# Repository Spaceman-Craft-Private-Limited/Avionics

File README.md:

Here the explanation of the uploaded .ino files content.
1. 80kv_BLDC.ino - In this file the code is written for a 80kv BLDC motor controlled by a 7Semi BLDC Motor Driver using ESP32 Dev kit.
The GPIO pin connections from 7semi BLDC driver to ESP32 are mentioned in the Code itself as Commented line.
2. all_in_one-damper_repulsion.ino - In this file the code is written for whole the prototype circuit, and in this file two types of code were written.
The first type is written that the stepper motor is controlled by the TB6600 motor driver and the whole code is commented.
The Second type is the code that the stepper motor is controlled by A4988 stepper motor driver and the whole code uncommented.
All the circuit connection is mentioned in the code itself and the Microcontroller used for this whole system is ESP32 Dev kit.
3. small_prototype_system_code_70rpm_noattraction.ino -  In this file the code is written to control the stepper motor by A4988 motor driver using Arduino uno microcontroller.
The term noattraction means the relay is always on, So the electromagnet connected in relay is always energized.
All the pins configurations are mentioned in the code itself.
4. small_prototype_system_code_70rpm_withattraction.ino - In this file the code is written to control the stepper motor by A4988 motor driver using Arduino uno microcontroller.
The term withattraction means the relay will turn on for few sec and turn off based on the logic given in code, So the electromagnet connected in relay will energized based on time.
All the pins configurations are mentioned in the code itself.

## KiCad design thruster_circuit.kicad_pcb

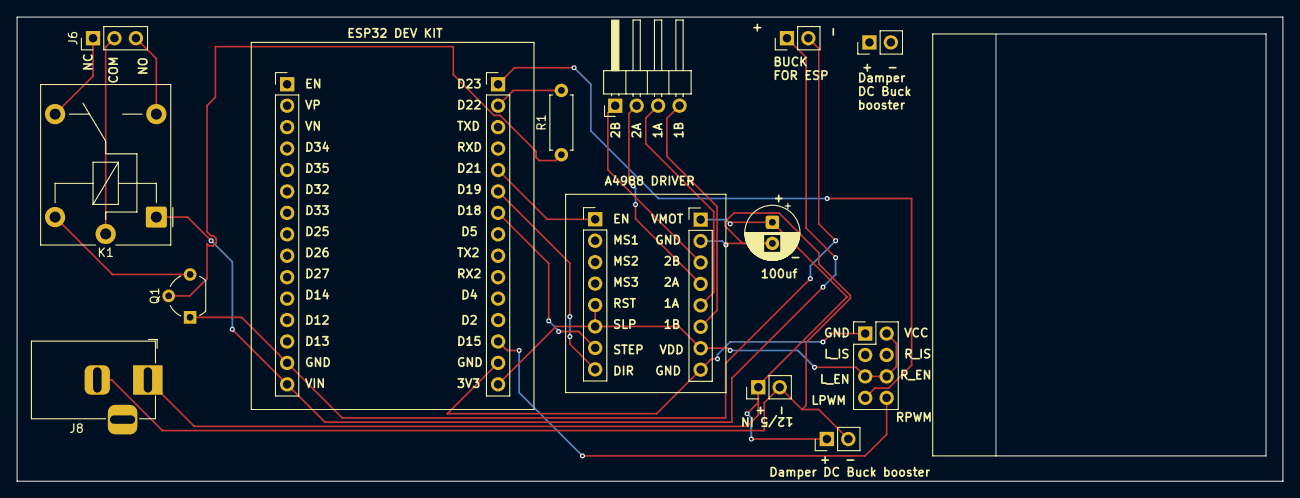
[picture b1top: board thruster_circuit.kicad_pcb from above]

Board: 2 copper layers, 150.0 x 55.0 mm, 16 parts (0 on the bottom side), 21 nets.

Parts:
C1: C; CP_Radial_D6.3mm_P2.50mm
J1, J2: Conn_01x15; PinHeader_1x15_P2.54mm_Vertical
J3, J4: Conn_01x08; PinHeader_1x08_P2.54mm_Vertical
J5: Conn_01x04; PinHeader_1x04_P2.54mm_Horizontal
J6: Conn_01x03; PinHeader_1x03_P2.54mm_Vertical
J7, J9, J10, J11: Conn_01x02; PinHeader_1x02_P2.54mm_Vertical
J8: Barrel_Jack; BarrelJack_Horizontal
J12: Conn_02x04_Top_Bottom; PinHeader_2x04_P2.54mm_Vertical
K1: Relay_SPDT; Relay_SPDT_Finder_36.11
Q1: 2N3904; TO-92_Wide
R1: R; R_Axial_DIN0207_L6.3mm_D2.5mm_P7.62mm_Horizontal

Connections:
unnamed: J1.14, J7.2, Q1.1 (E)
unnamed: J1.15, J7.1, K1.A1
unnamed: J2.2, R1.2
unnamed: J2.5, J3.1
unnamed: J2.6, J3.8
unnamed: J2.7, J3.7
unnamed: J4.3, J5.1
unnamed: J4.4, J5.2
unnamed: J4.5, J5.3
unnamed: J4.6, J5.4
unnamed: J6.1, K1.12
unnamed: J6.2, K1.11
unnamed: J6.3, K1.14
unnamed: C1.1, J4.1, J8.1, J9.1, J10.1
unnamed: C1.2, J4.2, J8.2, J9.2, J10.2
unnamed: J2.14, J4.8, J12.1
unnamed: J2.15, J3.5, J3.6, J4.7, J12.2, J12.5, J12.6
unnamed: J2.1, J12.7
unnamed: J2.13, J12.8
unnamed: Q1.2 (B), R1.1
unnamed: K1.A2, Q1.3 (C)

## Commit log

2025-09-05 Create Stepper Motor
2025-09-09 ino files explanationREADME.md
